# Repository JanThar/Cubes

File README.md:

- scad datei allgemeine datei. Wenn man di folgenden Sachen auf 1 setz kriegt man ne Aubauvorschau
  // Show lasercutted housing [0,1]
  showWall = 0;
  // Show lasercutted mechanics [0,1]
  showMechanics = 0;
  // Show 3D-printed parts [0,1]
  showPrint = 0;
  // Show axis and motors [0,1]
  showDrive = 0;
  // Show electronics [0,1]
  showElectronic = 0;
  bzw. mit // Flatten for lasercutting [0,1] flatten = 1;
  projection(cut = false) mechanics();
  oder
  projection(cut = false) walls();
  die Laserdateien und unter // 3D-printed die einzelnen 3D-Druckdateien
- svg für den laser, bei der Mechanics datei die z-achse platte und zahnstangen
  (links, zweite/dritte/vierte von oben) nicht cutten, wird vermutlich durch 3D druck ersetzt.
-  stl dateien zum drucken, Anzahl am Ende des Namens. Die 3 Toolhalter (Mill, Penholder, Laser)
  müssen noch mal überarbeitet werden (und dann zusammen mit z-Achsenplatte und Zahnstangen)

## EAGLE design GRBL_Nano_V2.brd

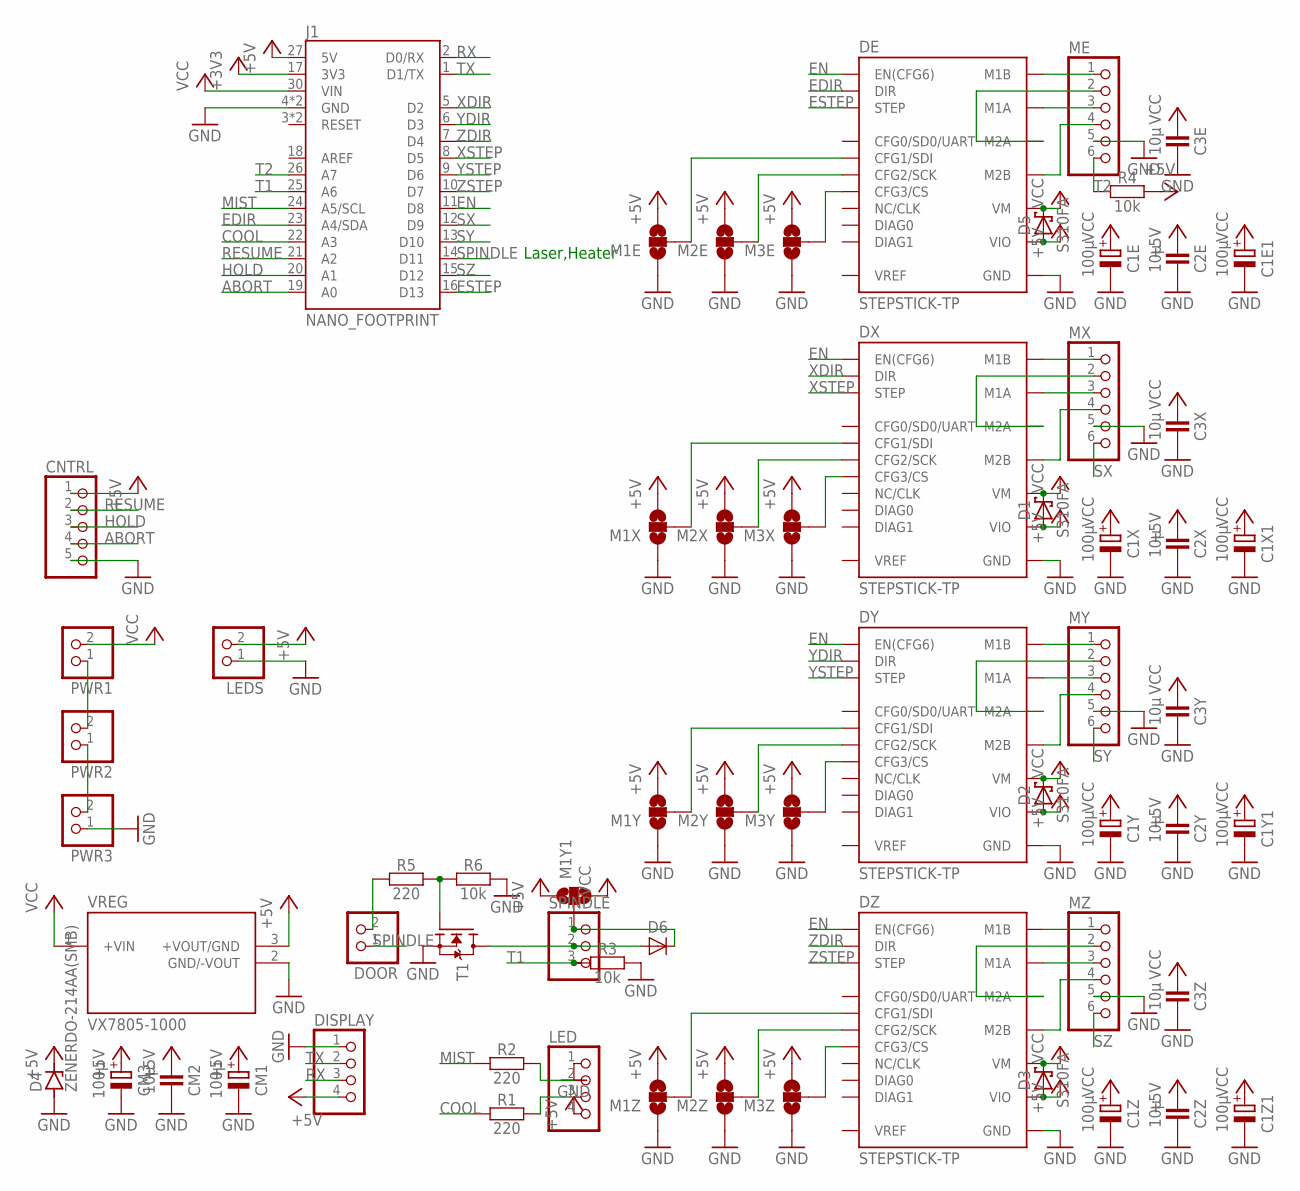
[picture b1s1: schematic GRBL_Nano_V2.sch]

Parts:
C1E, C1X, C1Y, C1Z: 100µ; C_8MM
C1E1, C1X1, C1Y1, C1Z1: 100µ; C_E5-10
C2E, C2X, C2Y, C2Z, C3E, C3X, C3Y, C3Z: 10µ; C0805
CM1: 100µ; C_8MM
CM2: 10µ; C0805
CM3: 100µ; C_E5-10
CNTRL: PINHD-1X5; 1X05
D1, D2, D3, D5: S310FA; SOD123
D4: ZENERDO-214AA(SMB); DIOM5336X265N
D6: DIODE-SMA; SMA_DO214AC
DE: STEPSTICK-TP; SSS_TP
DISPLAY: PINHD-1X4; 1X04
DOOR: PINHD-1X2; 1X02
DX: STEPSTICK-TP; SSS_TP
DY: STEPSTICK-TP; SSS_TP
DZ: STEPSTICK-TP; SSS_TP
J1: NANO_FOOTPRINT; NANO
LED: PINHD-1X4; 1X04
LEDS: PINHD-1X2; 1X02
M1E, M1X, M1Y, M1Y1, M1Z, M2E, M2X, M2Y, M2Z, M3E, M3X, M3Y, M3Z: SOLDERJUMPER_2WAY-OLDS; SJ_3
ME: PINHD-1X6; 1X06
MX: PINHD-1X6; 1X06
MY: PINHD-1X6; 1X06
MZ: PINHD-1X6; 1X06
PWR1, PWR2, PWR3: PINHD-1X2; 1X02
R1, R2, R5: 220; C0805
R3, R4, R6: 10k; C0805
SPINDLE: PINHD-1X3; 1X03
T1: MOSFET-N-DPAK; DPAK_TO252
VREG: VX7805-1000; VX78012-1000_VX7805-1000

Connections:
+3V3: J1.17 (3V3)
+5V: C2E.1, C2X.1, C2Y.1, C2Z.1, CM1.+, CM2.1, CM3.+, CNTRL.1, D1.A, D2.A, D3.A, D4.2 (C), D5.A, DE.VIO, DISPLAY.4, DX.VIO, DY.VIO, DZ.VIO, J1.27 (5V), LED.4, LEDS.2, M1E.3, M1X.3, M1Y.3, M1Y1.1, M1Z.3, M2E.3, M2X.3, M2Y.3, M2Z.3, M3E.3, M3X.3, M3Y.3, M3Z.3, R4.2, VREG.3 (+VOUT/GND)
ABORT: CNTRL.4, J1.19 (A0)
COOL: J1.22 (A3), R1.1
COOL1: LED.3, R1.2
EDIR: DE.DIR, J1.23 (A4/SDA)
EN: DE.EN (EN(CFG6)), DX.EN (EN(CFG6)), DY.EN (EN(CFG6)), DZ.EN (EN(CFG6)), J1.11 (D8)
ESTEP: DE.STEP, J1.16 (D13)
GND: C1E.-, C1E1.-, C1X.-, C1X1.-, C1Y.-, C1Y1.-, C1Z.-, C1Z1.-, C2E.2, C2X.2, C2Y.2, C2Z.2, C3E.2, C3X.2, C3Y.2, C3Z.2, CM1.-, CM2.2, CM3.-, CNTRL.5, D4.1 (A), DE.GND@1 (GND), DE.GND@2 (GND), DISPLAY.1, DX.GND@1 (GND), DX.GND@2 (GND), DY.GND@1 (GND), DY.GND@2 (GND), DZ.GND@1 (GND), DZ.GND@2 (GND), J1.4 (GND), J1.29 (GND), LED.1, LEDS.1, M1E.1, M1X.1, M1Y.1, M1Z.1, M2E.1, M2X.1, M2Y.1, M2Z.1, M3E.1, M3X.1, M3Y.1, M3Z.1, ME.5, MX.5, MY.5, MZ.5, PWR3.1, R3.2, R6.2, T1.3 (S), VREG.2 (GND/-VOUT)
HOLD: CNTRL.3, J1.20 (A1)
MIST: J1.24 (A5/SCL), R2.1
MIST1: LED.2, R2.2
unnamed: DX.M1A, MX.3
unnamed: DX.M2B, MX.4
unnamed: DX.M2A, MX.2
unnamed: DX.M1B, MX.1
unnamed: DZ.M1B, MZ.1
unnamed: DZ.M1A, MZ.3
unnamed: DY.M1B, MY.1
unnamed: DY.M1A, MY.3
unnamed: DY.M2A, MY.2
unnamed: DZ.M2A, MZ.2
unnamed: DZ.M2B, MZ.4
unnamed: DY.M2B, MY.4
unnamed: D6.A, SPINDLE.2, T1.2 (D)
unnamed: DOOR.2, R5.1
unnamed: DX.CFG1 (CFG1/SDI), M1X.2
unnamed: DX.CFG2 (CFG2/SCK), M2X.2
unnamed: DX.CFG3 (CFG3/CS), M3X.2
unnamed: DY.CFG1 (CFG1/SDI), M1Y.2
unnamed: DY.CFG2 (CFG2/SCK), M2Y.2
unnamed: DY.CFG3 (CFG3/CS), M3Y.2
unnamed: DZ.CFG1 (CFG1/SDI), M1Z.2
unnamed: DZ.CFG2 (CFG2/SCK), M2Z.2
unnamed: DZ.CFG3 (CFG3/CS), M3Z.2
unnamed: DE.M2B, ME.4
unnamed: DE.M1B, ME.1
unnamed: PWR1.1, PWR2.2
unnamed: D6.C, M1Y1.2, SPINDLE.1
unnamed: PWR2.1, PWR3.2
unnamed: DE.M1A, ME.3
unnamed: DE.M2A, ME.2
unnamed: DE.CFG1 (CFG1/SDI), M1E.2
unnamed: DE.CFG2 (CFG2/SCK), M2E.2
unnamed: DE.CFG3 (CFG3/CS), M3E.2
unnamed: R5.2, R6.1, T1.1 (G)
RESUME: CNTRL.2, J1.21 (A2)
RX: DISPLAY.3, J1.2 (D0/RX)
SPINDLE: DOOR.1, J1.14 (D11)
SX: J1.12 (D9), MX.6
SY: J1.13 (D10), MY.6
SZ: J1.15 (D12), MZ.6
T1: J1.25 (A6), R3.1, SPINDLE.3
T2: J1.26 (A7), ME.6, R4.1
TX: DISPLAY.2, J1.1 (D1/TX)
VCC: C1E.+, C1E1.+, C1X.+, C1X1.+, C1Y.+, C1Y1.+, C1Z.+, C1Z1.+, C3E.1, C3X.1, C3Y.1, C3Z.1, D1.C, D2.C, D3.C, D5.C, DE.VM, DX.VM, DY.VM, DZ.VM, J1.30 (VIN), M1Y1.3, PWR1.2, VREG.1 (+VIN)
XDIR: DX.DIR, J1.5 (D2)
XSTEP: DX.STEP, J1.8 (D5)
YDIR: DY.DIR, J1.6 (D3)
YSTEP: DY.STEP, J1.9 (D6)
ZDIR: DZ.DIR, J1.7 (D4)
ZSTEP: DZ.STEP, J1.10 (D7)

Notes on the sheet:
Laser,Heater

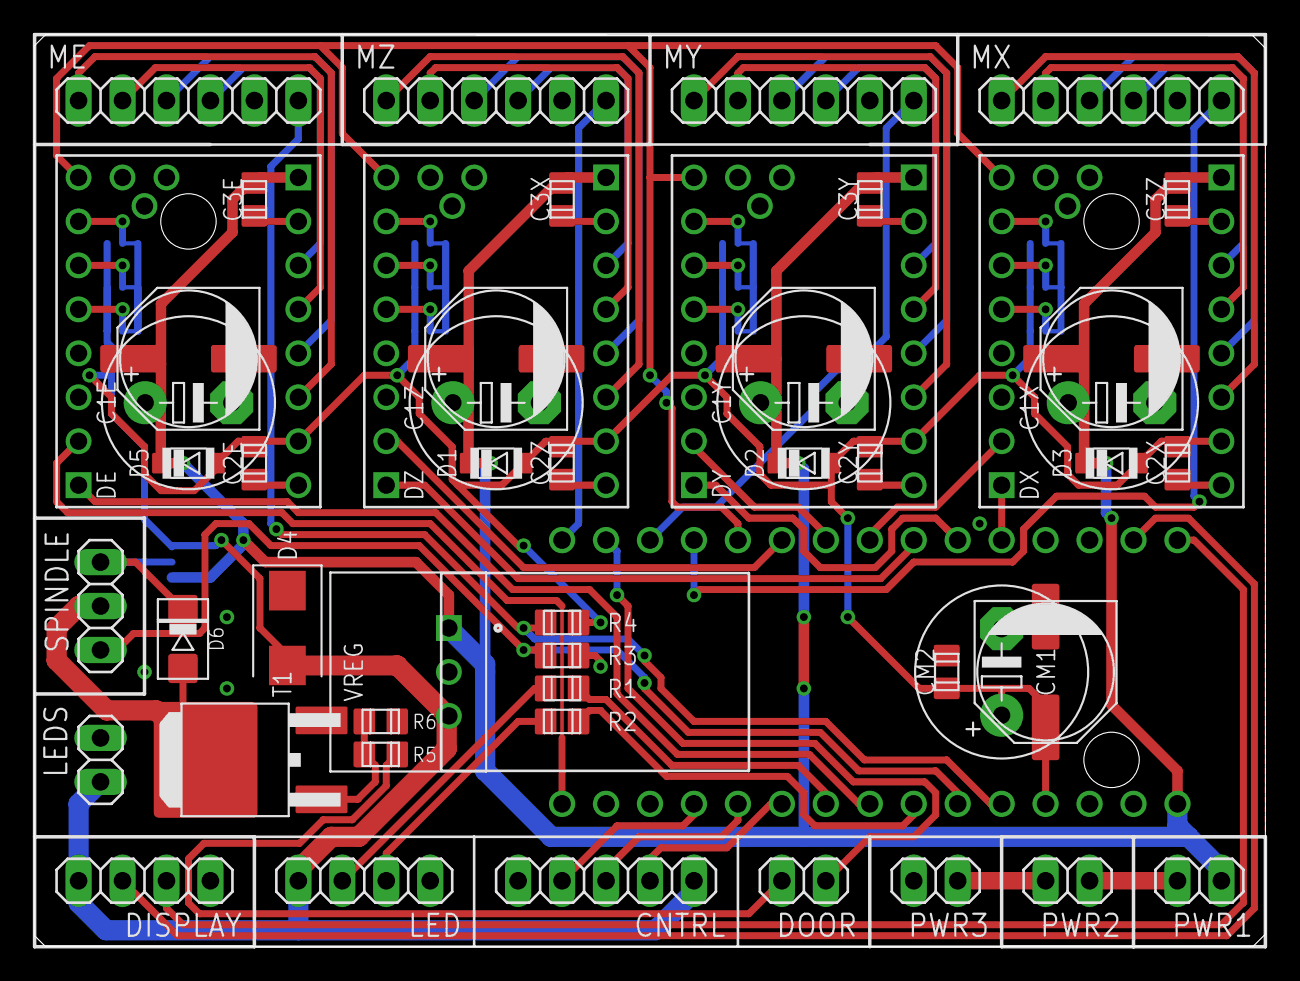
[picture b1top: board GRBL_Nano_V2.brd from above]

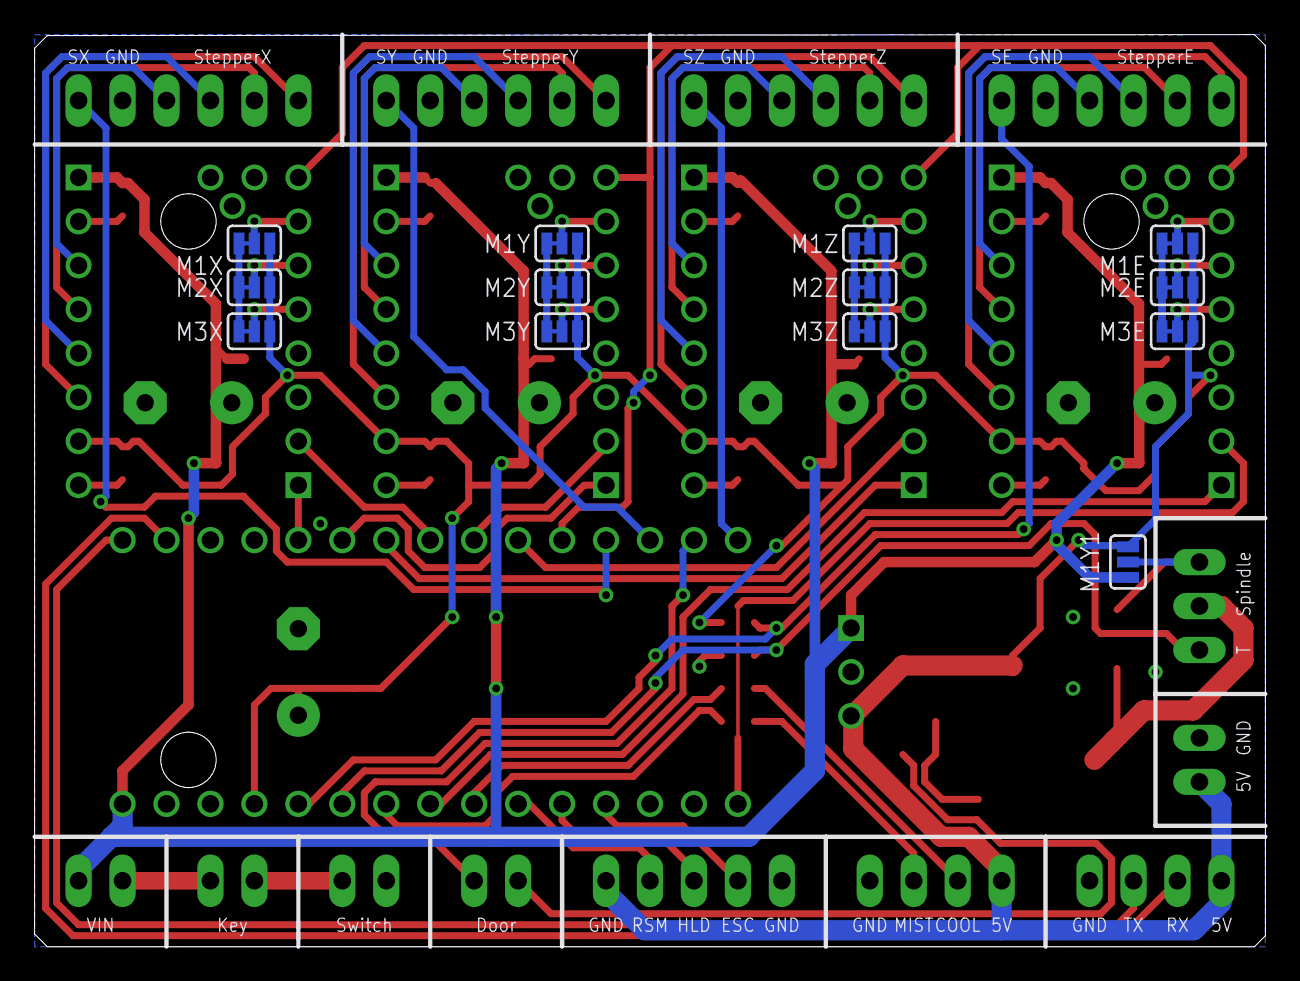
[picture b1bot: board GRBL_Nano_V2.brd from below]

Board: 2 copper layers, 71.1 x 52.7 mm, 64 parts (13 on the bottom side), 61 nets.

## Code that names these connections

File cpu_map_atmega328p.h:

/*
  cpu_map_atmega328p.h - CPU and pin mapping configuration file
  Part of Grbl

  Copyright (c) 2012-2015 Sungeun K. Jeon

  Grbl is free software: you can redistribute it and/or modify
  it under the terms of the GNU General Public License as published by
  the Free Software Foundation, either version 3 of the License, or
  (at your option) any later version.

  Grbl is distributed in the hope that it will be useful,
  but WITHOUT ANY WARRANTY; without even the implied warranty of
  MERCHANTABILITY or FITNESS FOR A PARTICULAR PURPOSE.  See the
  GNU General Public License for more details.

  You should have received a copy of the GNU General Public License
  along with Grbl.  If not, see <http://www.gnu.org/licenses/>.
*/

/* Grbl officially supports the Arduino Uno, but the other supplied pin mappings are
   supplied by users, so your results may vary. This cpu_map file serves as a central
   pin mapping settings file for AVR 328p used on the Arduino Uno.  */
   

// Additional:
// A7 Temperature E_Stepper (instead Endstop)
// A6 Temperature Spindle
#ifdef GRBL_PLATFORM
#error "cpu_map already defined: GRBL_PLATFORM=" GRBL_PLATFORM
#endif


#define GRBL_PLATFORM "Atmega328p"

// Define serial port pins and interrupt vectors.
#define SERIAL_RX     USART_RX_vect
#define SERIAL_UDRE   USART_UDRE_vect

// Define step pulse output pins. NOTE: All step bit pins must be on the same port.
#define STEP_DDR        DDRD
#define STEP_PORT       PORTD
#define X_STEP_BIT      5  // Uno Digital Pin 2
#define Y_STEP_BIT      6  // Uno Digital Pin 3
#define Z_STEP_BIT      7  // Uno Digital Pin 4
#define STEP_MASK       ((1<<X_STEP_BIT)|(1<<Y_STEP_BIT)|(1<<Z_STEP_BIT)) // All step bits

// Define step direction output pins. NOTE: All direction pins must be on the same port.
#define DIRECTION_DDR     DDRD
#define DIRECTION_PORT    PORTD
#define X_DIRECTION_BIT   2  // Uno Digital Pin 5
#define Y_DIRECTION_BIT   3  // Uno Digital Pin 6
#define Z_DIRECTION_BIT   4  // Uno Digital Pin 7
#define DIRECTION_MASK    ((1<<X_DIRECTION_BIT)|(1<<Y_DIRECTION_BIT)|(1<<Z_DIRECTION_BIT)) // All direction bits

// Define stepper driver enable/disable output pin.
#define STEPPERS_DISABLE_DDR    DDRB
#define STEPPERS_DISABLE_PORT   PORTB
#define STEPPERS_DISABLE_BIT    0  // Uno Digital Pin 8
#define STEPPERS_DISABLE_MASK   (1<<STEPPERS_DISABLE_BIT)

// Define homing/hard limit switch input pins and limit interrupt vectors. 
// NOTE: All limit bit pins must be on the same port, but not on a port with other input pins (CONTROL).
#define LIMIT_DDR        DDRB
#define LIMIT_PIN        PINB
#define LIMIT_PORT       PORTB
#define X_LIMIT_BIT      1  // Uno Digital Pin 9
#define Y_LIMIT_BIT      2  // Uno Digital Pin 10
#define Z_LIMIT_BIT	     4  // Uno Digital Pin 12
#define LIMIT_MASK       ((1<<X_LIMIT_BIT)|(1<<Y_LIMIT_BIT)|(1<<Z_LIMIT_BIT)) // All limit bits
#define LIMIT_INT        PCIE0  // Pin change interrupt enable pin
#define LIMIT_INT_vect   PCINT0_vect 
#define LIMIT_PCMSK      PCMSK0 // Pin change interrupt register

// Define spindle enable and spindle direction output pins.
#define SPINDLE_ENABLE_DDR    DDRB
#define SPINDLE_ENABLE_PORT   PORTB
#define SPINDLE_ENABLE_BIT    3  // Uno Digital Pin 11

#define E_STEP_DDR   DDRB
#define E_STEP_PORT  PORTB
#define E_STEP_BIT   5  // Uno Digital Pin 13 (NOTE: D13 can't be pulled-high input due to LED.)
#define E_DIR_DDR   DDRC
#define E_DIR_PORT  PORTC
#define E_DIR_BIT   4 // Uno Analog Pin 4 

// Define flood and mist coolant enable output pins.
// NOTE: Uno analog pins 4 and 5 are reserved for an i2c interface, and may be installed at
// a later date if flash and memory space allows.
#define COOLANT_FLOOD_DDR   DDRC
#define COOLANT_FLOOD_PORT  PORTC
#define COOLANT_FLOOD_BIT   3  // Uno Analog Pin 3
// ENABLE_M7 // Mist coolant disabled by default. See config.h to enable/disable.
#define COOLANT_MIST_DDR   DDRC
#define COOLANT_MIST_PORT  PORTC
#define COOLANT_MIST_BIT   5 // Uno Analog Pin 5 

// Define user-control controls (cycle start, reset, feed hold) input pins.
// NOTE: All CONTROLs pins must be on the same port and not on a port with other input pins (limits).
#define CONTROL_DDR       DDRC
#define CONTROL_PIN       PINC
#define CONTROL_PORT      PORTC
#define RESET_BIT         0  // Uno Analog Pin 0
#define FEED_HOLD_BIT     1  // Uno Analog Pin 1
#define CYCLE_START_BIT   2  // Uno Analog Pin 2
#define SAFETY_DOOR_BIT   1  // Uno Analog Pin 1 NOTE: Safety door is shared with feed hold. Enabled by config define.
#define CONTROL_INT       PCIE1  // Pin change interrupt enable pin
#define CONTROL_INT_vect  PCINT1_vect
#define CONTROL_PCMSK     PCMSK1 // Pin change interrupt register
#define CONTROL_MASK ((1<<RESET_BIT)|(1<<FEED_HOLD_BIT)|(1<<CYCLE_START_BIT)|(1<<SAFETY_DOOR_BIT))
#define CONTROL_INVERT_MASK CONTROL_MASK // May be re-defined to only invert certain control pins.
  
// Start of PWM & Stepper Enabled Spindle
#ifdef VARIABLE_SPINDLE
  // Advanced Configuration Below You should not need to touch these variables
  #define PWM_MAX_VALUE    255.0
  #define TCCRA_REGISTER	 TCCR2A
  #define TCCRB_REGISTER	 TCCR2B
  #define OCR_REGISTER     OCR2A
  
  #define COMB_BIT	     COM2A1
  #define WAVE0_REGISTER	 WGM20
  #define WAVE1_REGISTER	 WGM21
  #define WAVE2_REGISTER	 WGM22
  #define WAVE3_REGISTER	 WGM23
      
  // NOTE: On the 328p, these must be the same as the SPINDLE_ENABLE settings.
  #define SPINDLE_PWM_DDR	  DDRB
  #define SPINDLE_PWM_PORT  PORTB
  #define SPINDLE_PWM_BIT	  3    // Uno Digital Pin 11
#endif // End of VARIABLE_SPINDLE

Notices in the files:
parts and their libraries:
SparkFun-Retired: Licensing: Creative Commons ShareAlike 4.0 International - https://creativecommons.org/licenses/by-sa/4.0
